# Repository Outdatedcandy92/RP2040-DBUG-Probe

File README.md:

# RP2040 DBUG Probe

A RP2040 based debug probe; A USB device that provides a UART serial port and SWD interface.
Inspired by the [Raspberry Pi Debug Probe](https://www.raspberrypi.com/documentation/microcontrollers/debug-probe.html) I wanted to make my own debug probe as a fun project but implement custom features like a Type-C connector and regular (non JST) connectors while still keeping the original board footprint.

## Features

- RP2040 MCU (Duh)
- 16Mbit Flash
- USB-C Connector 
- 32mm X 22mm Board Footprint
- USB to UART/SWD Interfaces With Level Shifters
- Uses regular 2.54mm Pitch Headers
- Status LEDs for serial interfaces and power

## Table of Contents

- [Overview](#rp2040-dbug-probe)
- [Quick Start](#quick-start)
- [Hardware](#hardware)
	- [Pinout](#pinout)
	- [Schematic](#schematic)
	- [PCB](#pcb)
	- [Case](#case)
	- [BOM/Reproduction](#bomreproduction)
- [Firmware](#firmware)
- [License](#license)

## Quick Start

1. Hold the button on the board while plugging in the USB-C cable.
2. The board will appear as a mass storage device.
3. Drag and drop the `debugprobe.uf2` file from `/firmware` onto the device.

The RP2040 will reboot, and the status LED should turn green. It’s now ready to use as a USB-to-UART/SWD bridge.

To use it as a USB-to-UART adapter, open the corresponding COM port in your preferred tool and start communicating.

## Hardware

### Pinout

### Schematic

Schematic pdf is available under the `/hardware/PCB` folder and the project's KiCad files can be found under `/hardware/PCB/kicad`.

### PCB

### Case

The case files can be found under `/hardware/case`, It includes the STEP assembly file, and STLs for printing. 
Use the `top.stl` and `logo.stl` if you want to have the logo printed on top, if not use the `top_no_logo.stl`.

### BOM/Reproduction

The rough BOM can be found in [BOM.md](./BOM.md) and it assumes you'll assemble the board yourself. The rough cost for just the PCB and parts (excluding shipping) is around $24.

To build one yourself, use the files in `/hardware/production` to order the PCB and components, or opt for PCBA.

## Firmware

This project uses the [Debugprobe](https://github.com/raspberrypi/debugprobe?tab=readme-ov-file) firmware. To build one yourself for this board:

1. Clone the debug probe repository, cd into it and update the submodules.

```
git clone https://github.com/raspberrypi/debugprobe
cd debugprobe
git submodule update --init --recursive
```

2. Open  `/include/board_debug_probe_config.h` and edit the pin definitions to match the board.
   
3. Make a build directory and cd into it.

```
 mkdir build
 cd build
```

4. Run cmake and build the code.

>If your environment doesn't contain `PICO_SDK_PATH`, then either add it to your environment variables with `export PICO_SDK_PATH=/path/to/sdk` or add `-DPICO_SDK_PATH=/path/to/sdk` to the arguments to CMake below.

```
 cmake ..
 make
```

Once it successfully builds you should have a `debugprobe.uf2` file that you can upload to the board.

---

## License

This project is licensed under the CERN Open Hardware Licence Version 2 Weakly Reciprocal [(CERN OHL W)](LICENSE.txt)

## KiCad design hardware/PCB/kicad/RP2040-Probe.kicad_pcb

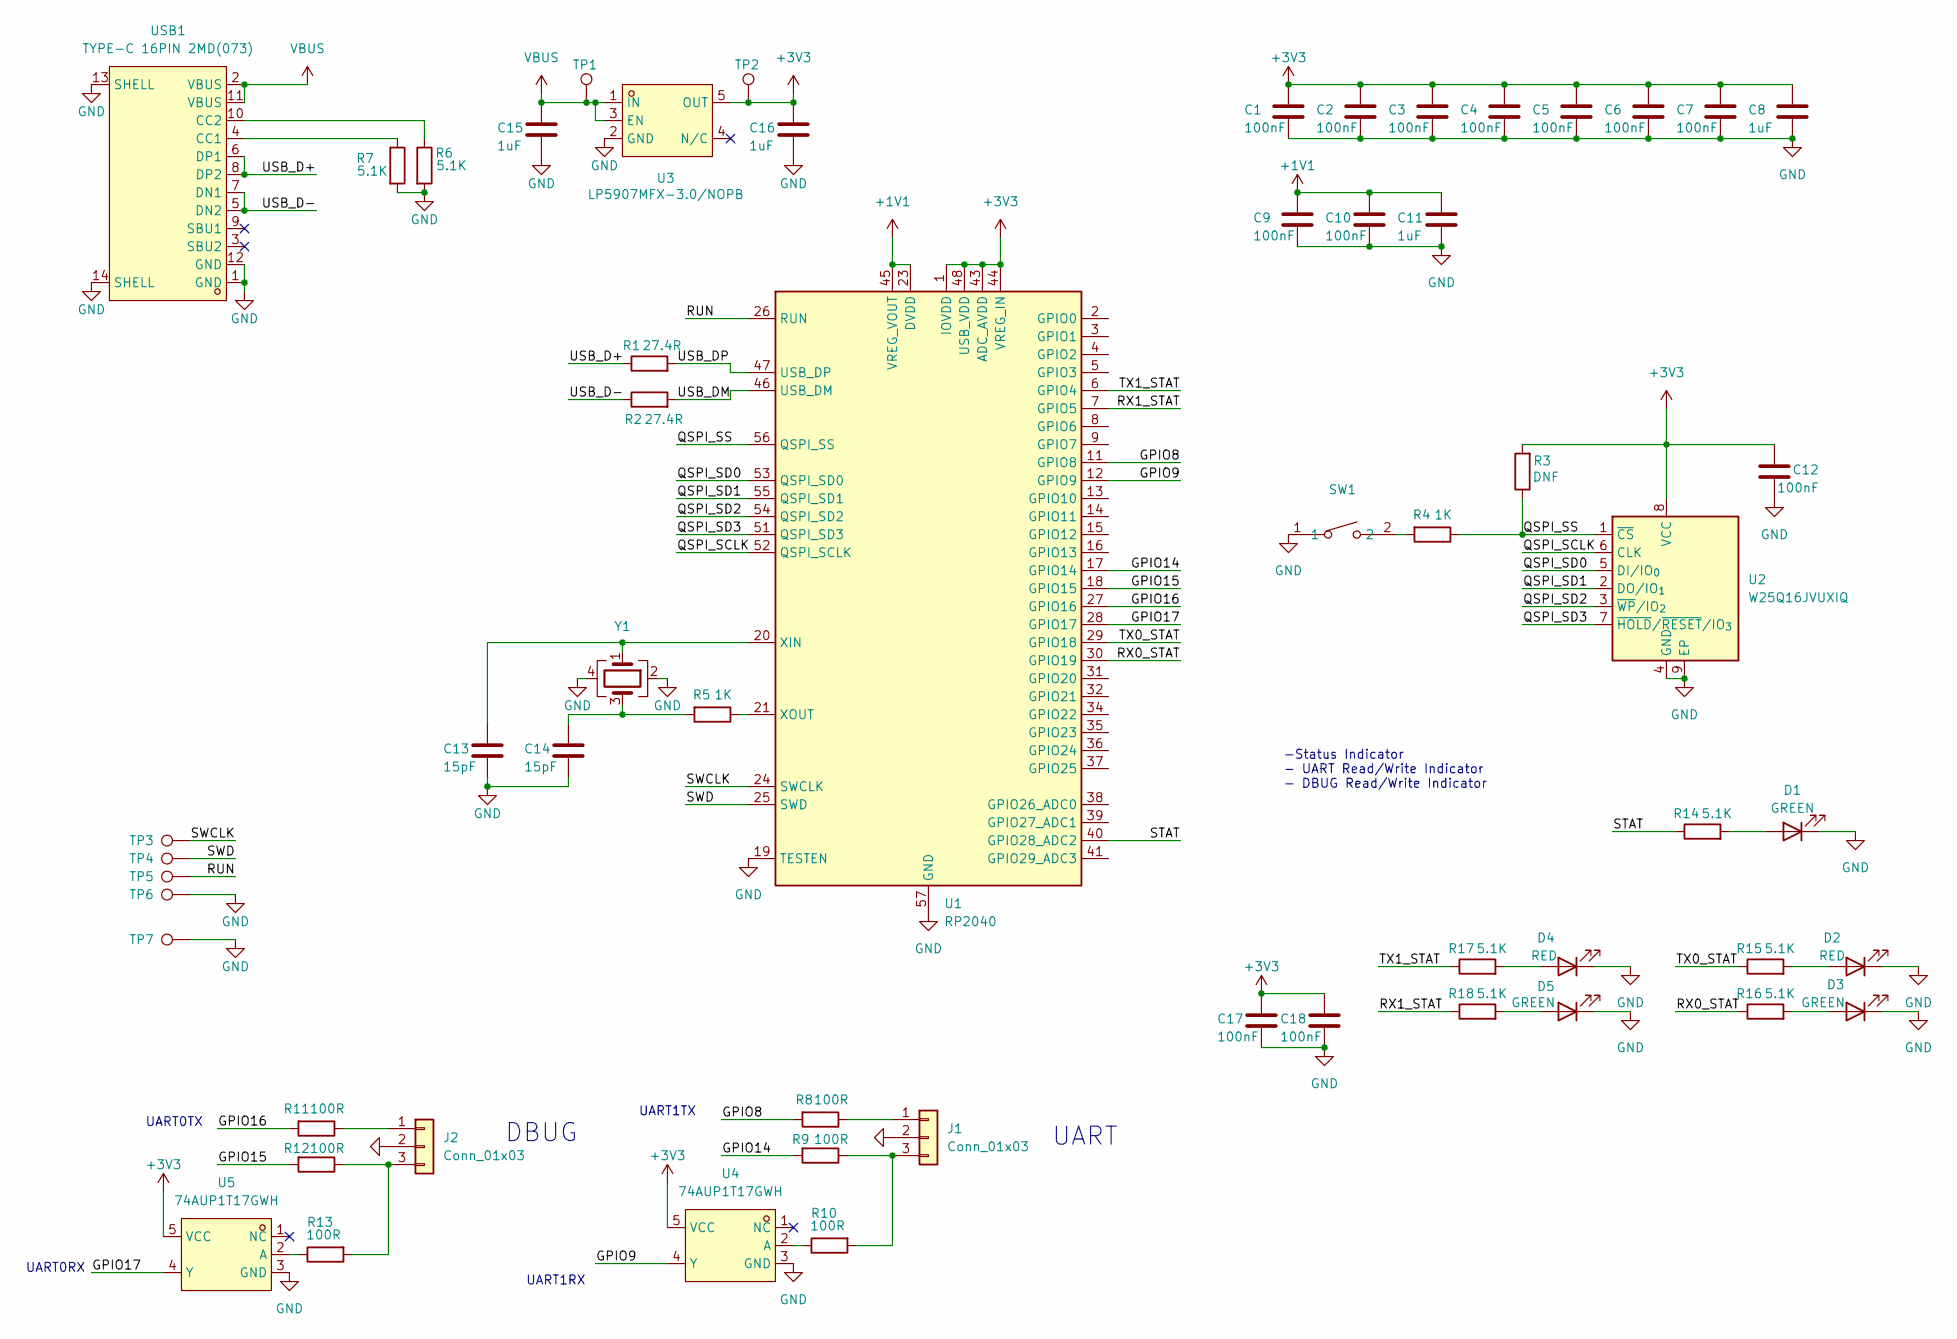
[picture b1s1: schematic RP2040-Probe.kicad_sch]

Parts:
C1, C2, C3, C4, C5, C6, C7, C9, C10, C12, C17, C18: 100nF; C_0402_1005Metric; LCSC Part C77020
C8, C11, C15, C16: 1uF; C_0402_1005Metric; LCSC Part C1518208
C13, C14: 15pF; C_0402_1005Metric; LCSC Part C441742
D1, D3, D5: GREEN; LED_0402_1005Metric; LCSC Part C965793
D2, D4: RED; LED_0402_1005Metric; LCSC Part C25503345
J1, J2: Conn_01x03; PinHeader_1x03_P2.54mm_Vertical; LCSC Part C52016391
R1, R2: 27.4R; R_0402_1005Metric; LCSC Part C31439
R3: DNF; R_0402_1005Metric
R4, R5: 1K; R_0402_1005Metric; LCSC Part C11702
R6, R7, R14, R15, R16, R17, R18: 5.1K; R_0402_1005Metric; LCSC Part C25905
R8, R9, R10, R11, R12, R13: 100R; R_0402_1005Metric; LCSC Part C25076
SW1: TS-1088-AR02016; SW-SMD_L3.9-W3.0-P4.45; LCSC Part C720477
TP1, TP2, TP3, TP4, TP5, TP6, TP7: TestPoint; TestPoint_Pad_1.0x1.0mm
U1: RP2040; QFN-56-1EP_7x7mm_P0.4mm_EP3.2x3.2mm; LCSC Part C2040
U2: W25Q16JVUXIQ; USON-8_L3.0-W2.0-P0.50-BL-EP; LCSC Part C2843335
U3: LP5907MFX-3.0/NOPB; SOT-23-5_L3.0-W1.7-P0.95-LS2.8-BL; LCSC Part C475492
U4, U5: 74AUP1T17GWH; TSSOP-5_L2.1-W1.3-P0.65-LS2.2-BR; LCSC Part C545951
USB1: TYPE-C 16PIN 2MD(073); USB-C-SMD_TYPE-C-6PIN-2MD-073; LCSC Part C2765186
Y1: Crystal_GND24; Crystal_SMD_Abracon_ABM8G-4Pin_3.2x2.5mm; LCSC Part C20625731

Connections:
+1V1: C9.1, C10.1, C11.1, U1.23 (DVDD), U1.45 (VREG_VOUT), U1.50 (DVDD)
+3V3: C1.1, C2.1, C3.1, C4.1, C5.1, C6.1, C7.1, C8.1, C12.1, C16.1, C17.1, C18.1, R3.2, TP2.1, U1.1 (IOVDD), U1.10 (IOVDD), U1.22 (IOVDD), U1.33 (IOVDD), U1.42 (IOVDD), U1.43 (ADC_AVDD), U1.44 (VREG_IN), U1.48 (USB_VDD), U1.49 (IOVDD), U2.8 (VCC), U3.5 (OUT), U4.5 (VCC), U5.5 (VCC)
/GPIO8: R8.2, U1.11 (GPIO8)
/GPIO9: U1.12 (GPIO9), U4.4 (Y)
/GPIO14: R9.2, U1.17 (GPIO14)
/GPIO15: R12.2, U1.18 (GPIO15)
/GPIO16: R11.2, U1.27 (GPIO16)
/GPIO17: U1.28 (GPIO17), U5.4 (Y)
/QSPI_SCLK: U1.52 (QSPI_SCLK), U2.6 (CLK)
/QSPI_SD0: U1.53 (QSPI_SD0), U2.5 (DI/IO_{0})
/QSPI_SD1: U1.55 (QSPI_SD1), U2.2 (DO/IO_{1})
/QSPI_SD2: U1.54 (QSPI_SD2), U2.3 (~WP/IO_{2})
/QSPI_SD3: U1.51 (QSPI_SD3), U2.7 (~HOLD/~RESET/IO_{3})
/QSPI_SS: R3.1, R4.1, U1.56 (QSPI_SS), U2.1 (~CS)
/RUN: TP5.1, U1.26 (RUN)
/RX0_STAT: R18.1, U1.7 (GPIO5)
/RX1_STAT: R16.1, U1.30 (GPIO19)
/STAT: R14.1, U1.40 (GPIO28_ADC2)
/SWCLK: TP3.1, U1.24 (SWCLK)
/SWD: TP4.1, U1.25 (SWD)
/TX0_STAT: R17.1, U1.6 (GPIO4)
/TX1_STAT: R15.1, U1.29 (GPIO18)
/USB_D+: R1.1, USB1.6 (DP1), USB1.8 (DP2)
/USB_D-: R2.1, USB1.5 (DN2), USB1.7 (DN1)
/USB_DM: R2.2, U1.46 (USB_DM)
/USB_DP: R1.2, U1.47 (USB_DP)
GND: C1.2, C2.2, C3.2, C4.2, C5.2, C6.2, C7.2, C8.2, C9.2, C10.2, C11.2, C12.2, C13.2, C14.2, C15.2, C16.2, C17.2, C18.2, D1.1 (K), D2.1 (K), D3.1 (K), D4.1 (K), D5.1 (K), J1.2, J2.2, R6.2, R7.2, SW1.1, TP6.1, TP7.1, U1.19 (TESTEN), U1.57 (GND), U2.4 (GND), U2.9 (EP), U3.2 (GND), U4.3 (GND), U5.3 (GND), USB1.1 (GND), USB1.12 (GND), USB1.13 (SHELL), USB1.14 (SHELL), Y1.2, Y1.4
unnamed: C14.1, R5.2, Y1.3
unnamed: D1.2 (A), R14.2
unnamed: D2.2 (A), R15.2
unnamed: D3.2 (A), R16.2
unnamed: D4.2 (A), R17.2
unnamed: D5.2 (A), R18.2
unnamed: J1.1, R8.1
unnamed: J1.3, R9.1, R10.2
unnamed: J2.1, R11.1
unnamed: J2.3, R12.1, R13.2
unnamed: R4.2, SW1.2
unnamed: C13.1, U1.20 (XIN), Y1.1
unnamed: R5.1, U1.21 (XOUT)
unnamed: R10.1, U4.2 (A)
unnamed: R13.1, U5.2 (A)
unnamed: R7.1, USB1.4 (CC1)
unnamed: R6.1, USB1.10 (CC2)
VBUS: C15.1, TP1.1, U3.1 (IN), U3.3 (EN), USB1.2 (VBUS), USB1.11 (VBUS)

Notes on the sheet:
UART
UART1TX
UART1RX
-Status Indicator - UART Read/Write Indicator - DBUG Read/Write Indicator
UART0RX
DBUG
UART0TX

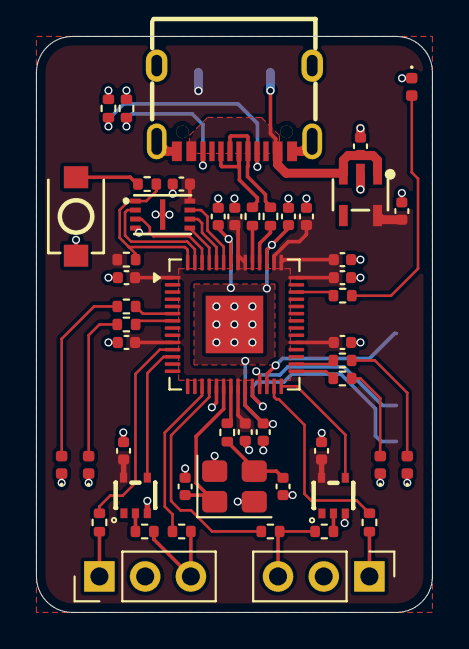
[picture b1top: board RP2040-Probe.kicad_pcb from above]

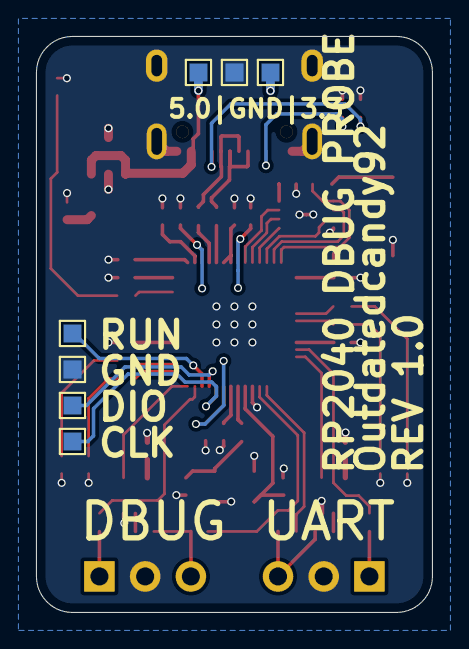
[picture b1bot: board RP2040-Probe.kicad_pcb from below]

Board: 2 copper layers, 22.0 x 32.0 mm, 58 parts (7 on the bottom side), 45 nets.

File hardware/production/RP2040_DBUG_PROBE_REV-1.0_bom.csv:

Designator,Footprint,Quantity,Value,LCSC Part #
"C1, C10, C12, C17, C18, C2, C3, C4, C5, C6, C7, C9",0402,12,100nF,
"C11, C15, C16, C8",0402,4,1uF,
"C13, C14",0402,2,15pF,
"D1, D2, D3, D4, D5",0402,5,LED,
"J1, J2",PinHeader_1x03_P2.54mm_Vertical,2,Conn_01x03,
"R1, R2",0402,2,27.4R,
"R10, R11, R12, R13, R8, R9",0402,6,100R,
"R14, R15, R16, R17, R18, R6, R7",0402,7,5.1K,
R3,0402,1,DNF,
"R4, R5",0402,2,1K,
SW1,SW-SMD_L3.9-W3.0-P4.45,1,TS-1088-AR02016,C720477
"TP1, TP2, TP3, TP4, TP5, TP6, TP7",TestPoint_Pad_1.0x1.0mm,7,TestPoint,
U1,QFN-56-1EP_7x7mm_P0.4mm_EP3.2x3.2mm,1,RP2040,
U2,USON-8_L3.0-W2.0-P0.50-BL-EP,1,W25Q16JVUXIQ,
U3,SOT-23-5_L3.0-W1.7-P0.95-LS2.8-BL,1,LP5907MFX-3.3/NOPB,C80670
"U4, U5",TSSOP-5_L2.1-W1.3-P0.65-LS2.2-BR,2,74AUP1T17GWH,C545951
USB1,USB-C-SMD_TYPE-C-6PIN-2MD-073,1,TYPE-C 16PIN 2MD(073),C2765186
Y1,Crystal_SMD_Abracon_ABM8G-4Pin_3.2x2.5mm,1,Crystal_GND24,

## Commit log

2026-03-23 build
2026-03-23 attachments folder
2026-03-23 journal update
2026-03-23 fix table of content links
2026-03-24 Correct production files path in README
    Updated the path for production files in the README.
